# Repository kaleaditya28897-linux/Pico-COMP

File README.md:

# Pico-COMP

**A modern take on the TRS-80 Model 100: a text-only, battery-powered portable computer built on two
Raspberry Pi RP2350 microcontrollers.**

Pico-COMP is a clamshell laptop for writing and focused work: a full-size mechanical keyboard, a 7"
display driven in 80-column text mode (amber, green or white on black), a week of standby on a 2S2P
18650 pack, and Wi-Fi for mail, chat and file sync. Everything is programmed in C on the RP2350's RISC-V
cores, and every board, case part and keycap is generated from scripts in this repository.

> **Status (Nov 2026):** both boards, the switch plate, keycaps and battery spec are ready to order. The
> main board is routed and passes ERC, DRC (with schematic parity) and a power-copper audit; the case
> prints wait for the measured battery pack and display. Firmware: display driver and project skeleton.

| Part | State |
|---|---|
| Keyboard PCB (2 layers) | Routed, KiCad DRC 0 / ERC 0, fab package in `hardware/fab/keyboard/` |
| Switch plate | Laser-cut DXF ready (1.2 mm) |
| Keycaps (75) | Print-ready STEP/STL with debossed legends + inlays |
| Main board (6 layers) | Routed, ERC 0 / DRC 0 / power audit pass, fab package + order sheet in `hardware/fab/mainboard/` |
| Case | Parametric FreeCAD assembly, printable parts, no interferences |
| Firmware | Builds for both MCUs; HSTX DVI text driver (untested on hardware) |

---

## Features

- **Display:** 7" 1024x600 IPS HDMI panel fed 720x400 / 640x480 DVI straight from the RP2350's HSTX
  peripheral, as 80x25 / 80x30 text; amber-on-black, green-on-black and black-on-white schemes.
- **Keyboard:** 75 keys, Kailh Choc V1 low-profile switches at 17 mm pitch, inverted-T arrows (the only
  navigation), Fn layer for hotkeys, Kailh plate-mount stabilizers on Shift and Space.
- **Storage:** 64 GB soldered eMMC (internal disk) plus a microSD slot for extra space / file exchange;
  16 MB QSPI flash per MCU for firmware.
- **Wireless:** Wi-Fi 4 + Bluetooth 5.2 (Raspberry Pi RM2 / CYW43439, the Pico 2 W radio).
- **USB:**
  - USB-C port 1: dual-role (TUSB320). Device mode for charging, flashing, file transfer and serial;
    host mode for USB printers, barcode scanners and keyboards.
  - USB-C port 2: the network MCU's own USB.
- **Power:** custom 2S2P 18650 pack (7.4 V, 44 Wh), TI BQ25798 USB-C buck-boost charger, 5 V and 3.3 V
  buck converters, switched panel power for standby. Target: one week standby, ~4 days of normal use.
- **Buttons:** a real power button (charger ship mode disconnects the pack through a ship FET; press to
  turn on, hold 10 s for a hardware power cycle) and a system-reset pinhole that resets both MCUs.
- **I/O:** serial printer port (JST-SH, UART with RTS/CTS), expansion header (6 GPIO + I2C/SPI),
  piezo beeper.
- **Software (planned):** text editor, spreadsheet, database, mail, IM (IRC/Matrix), file sync web
  page, scheduler, todo, BASIC calculator, SSH/terminal, Gopher/Gemini, RSS, games. See `intent.md`.

## Architecture

Two RP2350s split the work so the UI never stalls on the network:

```
            USB-C 1 (dual-role)            HDMI (internal) -> 7" panel
                  |                              ^
   +--------------+------------------------------+--------------------+
   |  UI MCU: RP2350B (QFN-80)                                        |
   |  HSTX DVI text display, all apps, eMMC 64 GB (PIO 4-bit),        |
   |  microSD (SPI0), printer UART1, expansion, beeper, panel power   |
   +--------------+---------------------------------+-----------------+
                  | UART0 link (framed packets)     | SWD (UI reflashes NET)
   +--------------+---------------------------------+-----------------+
   |  NET MCU: RP2350A (QFN-60)                                       |
   |  Wi-Fi/BT (RM2, PIO gSPI), keyboard matrix scan (6x14),          |
   |  BQ25798 charger + TUSB320 over I2C, USB-C 2                     |
   +-------------------------------------------------------------------+
```

- Inter-MCU protocol: `[0xA5][type][len][payload][crc8]`, see `firmware/common/link.h`.
- Full GPIO map for both MCUs: `firmware/common/pins.h`.
- Design notes: `docs/architecture.md`, `docs/hardware-plan.md`.

## Firmware updates

- **Normal update:** connect USB-C port 1 to a computer. An "update firmware" hotkey (or
  `picotool reboot -u`) puts the UI MCU into the RP2350 USB bootloader, where it appears as a drive. Copy
  one `.uf2`. The UI image carries the NET MCU firmware and rewrites it over SWD when the version differs.
- **Recovery:** double-tap the system-reset button through the pinhole in the right side wall, which
  brings up the USB update drive (`pico_bootsel_via_double_reset`). If anything hangs, hold the power
  button for 10 s: the charger power-cycles the whole machine. BOOTSEL buttons inside the case are the last
  resort.
- **NET MCU direct:** USB-C port 2.

## Repository layout

```
firmware/            C firmware (Pico SDK, RISC-V)
  ui/                UI MCU: HSTX DVI text driver, font, main
  net/               NET MCU (stub)
  common/            link protocol, pin map
  boards/            pico_comp.h board header (16 MB flash, per-target RP2350A/B)
hardware/
  keyboard/          layout.py (single source of key positions), PCB + schematic generators
  mainboard/         PCB + schematic generators, fan-out, routers (Freerouting driver, maze router)
  kicad/             KiCad 10 projects, project libraries (footprints, symbols, 3D models), helpers
  mechanical/        FreeCAD case/assembly generator, keycaps, renders, print files
  fab/               fabrication packages and order sheets
  placement.py       where the boards sit in the case
docs/                architecture, hardware plan, routing guide, case dimensions
tools/               font converter
```

## Building the firmware

Requirements: [Raspberry Pi Pico SDK](https://github.com/raspberrypi/pico-sdk) 2.x and a RISC-V
toolchain (`riscv32-unknown-elf`, as distributed for the Pico SDK).

```sh
export PICO_SDK_PATH=~/pico-sdk          # default
export RISCV_TC=~/toolchains/riscv        # default
./build.sh
# -> build/firmware/ui/comp_ui.uf2, build/firmware/net/comp_net.uf2
cmake --build build --target comp_ui     # rebuild one target
```

Firmware is C11 only. The board header `firmware/boards/pico_comp.h` describes this hardware; the UI
target is built for the RP2350B package (`PICO_RP2350A=0`).

## Hardware

Nothing under `hardware/` is drawn by hand: every board, schematic, footprint, 3D model, case part and
keycap is generated by the Python scripts next to it, and opened and checked in KiCad / FreeCAD.

| Board | Size | Layers | Notes |
|---|---|---|---|
| Main board | 152 x 84 mm | 6 (sig / GND / sig / sig / 3V3 / sig) | 5-mil rules, 0.45/0.2 vias, via-in-pad under the eMMC BGA |
| Keyboard | 244 x 120 mm | 2 | 75 Choc V1 (top, THT), 75 diodes (bottom, SMD) |

Key parts: RP2350A + RP2350B, W25Q128JV flash x2, BQ25798 charger, TPS62933 (5 V) and AP63203 (3.3 V)
bucks, TPS22917 panel switch, TUSB320 USB-C controller, Raspberry Pi RM2, 64 GB eMMC (Kimtigo
KM110SS1064GxA), Hirose microSD, Molex HDMI, HRO USB-C x2, XT30 battery connector.

### Tools
- KiCad 10 (with `pcbnew` Python), FreeCAD 1.x (`FreeCADCmd`), Java 21 + Freerouting 2.1 (routing only).

### Regenerating
The full order is at the end of `docs/hardware-plan.md`. In short:

```sh
python3 hardware/keyboard/layout.py                        # key positions, plate.dxf
python3 hardware/kicad/make_footprints.py                  # RM2, Choc and stabilizer footprints
FreeCADCmd hardware/kicad/make_3d.py                       # STEP models missing from KiCad's library
python3 hardware/mainboard/gen_pcb.py && python3 hardware/mainboard/gen_sch.py
python3 hardware/keyboard/gen_pcb.py  && python3 hardware/keyboard/gen_sch.py
python3 hardware/mainboard/fanout.py hardware/kicad/mainboard.kicad_pcb    # plane, BGA, dog-bone fan-out
ROUTE_EXTRA=--router.job_timeout=00:40:00 python3 hardware/mainboard/route.py hardware/kicad/<board>.kicad_pcb 40
python3 hardware/mainboard/maze_route.py hardware/kicad/<board>.kicad_pcb  # finish leftovers (route_from.py)
python3 hardware/mainboard/route.py --prune hardware/kicad/<board>.kicad_pcb
python3 hardware/mainboard/check_power.py hardware/kicad/mainboard.kicad_pcb  # power-copper gate
sh hardware/kicad/fab.sh                                   # ERC/DRC gate + all fab outputs
python3 hardware/kicad/export_parts.py && FreeCADCmd hardware/mechanical/case.py
FreeCAD hardware/mechanical/open_gui.py                    # open the assembly (saves colours)
```

Schematic and PCB are generated from one netlist and linked symbol-to-footprint, so ERC and
schematic-parity DRC must stay at zero. `fab.sh` refuses to export a board that fails either.

### Case and keycaps
- Laptop-style split: bottom tub (D-cover), top deck (C-cover) flush with the rim, lid shell + back
  cover, hinge on a steel pin. 250 x 140 mm footprint, 52 mm closed.
- Printable parts (STEP + STL) in `hardware/mechanical/print/`: base, deck, lid, lid back.
- Keycaps in `hardware/mechanical/keycaps/`: Choc V1 stems, legends debossed 0.5 mm with matching
  inlay bodies for two-colour printing; Shift/Space carry stabilizer pegs.
- Review renders: `FreeCADCmd hardware/mechanical/render_export.py && python3 hardware/mechanical/render.py`.

## Ordering

Everything is set up for [robu.in](https://robu.in) (PCB fab + assembly, laser cutting, 3D printing,
custom Li-ion packs); the files are standard and work with any fab.

- What goes where: `hardware/fab/ORDER-CHECKLIST.md`
- Keyboard PCB order sheet: `hardware/fab/keyboard/ORDER.md` (assemble the diodes only; the switches
  are soldered after they are clipped into the plate)

## Open items

- Measure the display module (thickness, outline) and the HDMI cable; adjust the lid.
- Size the battery bay to the delivered pack.
- Firmware: key scanner, UART link, eMMC (PIO SD/MMC) and USB host drivers, NET reflash over SWD,
  file system, apps; power key (GPIO37) and power-off via the charger's ship mode (SDRV_CTRL = 10),
  charge-current limit (<= 2 A, the BAT copper is sized for it).

## Credits

Designed by Aditya Kale. Terminus font (SIL OFL 1.1). Built on the Raspberry Pi Pico SDK, KiCad,
FreeCAD and Freerouting.

© 2026 Aditya Kale. Licensed under the GNU General Public License v3.0, see [LICENSE](LICENSE).

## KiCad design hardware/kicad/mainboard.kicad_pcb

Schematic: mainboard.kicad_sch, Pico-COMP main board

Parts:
BZ1: Piezo; Buzzer_Murata_PKMCS0909E; MPN PKMCS0909E4000-R1
C11, C12, C13, C14, C15, C16, C17, C18, C19, C21, C22, C23, C24, C25, C26, C27, C28, C29, C62, C71, C80, C90, C100, C110, C111, C113, C114, C122, C222: 100nF; C_0402_1005Metric
C50, C51, C52, C53, C57, C58, C59, C60, C61, C68, C70, C81, C510: 10uF; C_0805_2012Metric
C54, C55: 47nF; C_0402_1005Metric
C56, C112, C115: 4.7uF; C_0603_1608Metric
C63, C512: 10nF; C_0402_1005Metric
C64, C65, C66, C72, C73, C74: 22uF; C_0805_2012Metric
C67, C116: 1uF; C_0402_1005Metric
C69: 1nF; C_0402_1005Metric
C120, C121, C220, C221: 4.7uF; C_0402_1005Metric_RPi_Wide; MPN GRM155R60J475ME47D
C123, C124, C223, C224: 15pF; C_0402_1005Metric
C125, C225: 4.7uF; C_0402_1005Metric; MPN GRM155R60J475ME47D
D1: PWR; LED_0603_1608Metric
D2: UI; LED_0603_1608Metric
D50, D51: BAT54C; SOT-23; MPN BAT54C
F1, F2: W25Q128JVS; SOIC-8_5.3x5.3mm_P1.27mm; MPN W25Q128JVSIQ
FID1, FID2, FID3: Fiducial; Fiducial_1mm_Mask2mm
H1, H2, H3, H4: M2.5; MountingHole_2.7mm_M2.5
J1: USB-C; USB_C_Receptacle_HRO_TYPE-C-31-M-12; MPN TYPE-C-31-M-12
J2: BATTERY 2S; AMASS_XT30PW-M_1x02_P2.50mm_Horizontal; MPN XT30PW-M
J3, J4: SWD; PinHeader_1x03_P1.27mm_Vertical_SMD_Pin1Left
J5: NTC; JST_PH_B2B-PH-K_1x02_P2.00mm_Vertical; MPN B2B-PH-K-S
J6: HDMI to panel; HDMI_A_Molex_208658-1001_Horizontal; MPN 2086581001
J7: PANEL 5V; JST_PH_B2B-PH-K_1x02_P2.00mm_Vertical; MPN B2B-PH-K-S
J8: AUX 5V; JST_PH_B2B-PH-K_1x02_P2.00mm_Vertical; MPN B2B-PH-K-S
J9: microSD; microSD_HC_Hirose_DM3AT-SF-PEJM5; MPN DM3AT-SF-PEJM5
J11: KB_MATRIX; PinHeader_1x20_P2.54mm_Horizontal
J12: PRINTER; JST_SH_SM06B-SRSS-TB_1x06-1MP_P1.00mm_Horizontal; MPN SM06B-SRSS-TB
J13: EXPANSION; PinHeader_1x10_P1.27mm_Vertical
J14: USB-C NET; USB_C_Receptacle_HRO_TYPE-C-31-M-12; MPN TYPE-C-31-M-12
L1, L2: 3.3uH; L_Abracon_AOTA-B201610S_RPi; MPN AOTA-B201610S3R3-101-T
L5: 2.2uH; L_Bourns_SRP7028A_7.3x6.6mm; MPN SRP7028A-2R2M
L6: 4.7uH; L_Bourns_SRP7028A_7.3x6.6mm; MPN SRP7028A-4R7M
L7: 4.7uH; L_Bourns_SRN6045TA; MPN SRN6045TA-4R7M
Q50: CSD17581Q3A; VSON-8_3.3x3.3mm_P0.65mm_TI_Q3A; MPN CSD17581Q3A
R11, R12, R21, R22, R95: 1k; R_0402_1005Metric
R13, R23, R56, R57, R61, R90, R91, R92, R97, R110, R111, R112, R113, R114, R115, R130: 10k; R_0402_1005Metric
R14, R24: 33; R_0402_1005Metric
R50: 5.23k; R_0402_1005Metric
R51: 30.1k; R_0402_1005Metric
R52, R53, R116, R117, R118, R119: 47k; R_0402_1005Metric
R54, R55, R70: 4.7k; R_0402_1005Metric
R58: 8.2k; R_0402_1005Metric
R59, R98: 100; R_0402_1005Metric
R60: 52.3k; R_0402_1005Metric
R80, R81, R82, R83, R84, R85, R86, R87: 270; R_0402_1005Metric
R96: 470; R_0402_1005Metric
R99: 100k; R_0402_1005Metric
R100: 887k; R_0402_1005Metric
RCC3, RCC4: 5.1k; R_0402_1005Metric
RNU1, RNU2: 27; R_0402_1005Metric
RUD1, RUD2: 27; R_0402_1005Metric
SW1, SW3: BOOTSEL; SW_SPST_B3U-1000P; MPN B3U-1000P
SW2: RESET; Panasonic_EVQPUJ_EVQPUA; MPN EVQ-PUJ02K
SW4: RESET; SW_SPST_B3U-1000P; MPN B3U-1000P
SW5: POWER; Panasonic_EVQPUJ_EVQPUA; MPN EVQ-PUJ02K
U1: RP2350B (UI); QFN-80-1EP_10x10mm_P0.4mm_EP3.4x3.4mm; MPN RP2350B
U2: RP2350A (NET); QFN-60-1EP_7x7mm_P0.4mm_EP3.4x3.4mm; MPN RP2350A
U3, U11: USBLC6-2SC6; SOT-23-6; MPN USBLC6-2SC6
U5: BQ25798; Texas_RQM0029A_VQFN-29_4x4mm_P0.4mm; MPN BQ25798RQMR
U6: TPS62933; SOT-583-8; MPN TPS62933DRLR
U7: AP63203WU; TSOT-23-6; MPN AP63203WU-7
U8: RM2; RaspberryPi_RM2; MPN RMC20452T
U9: TPS22917; SOT-23-6; MPN TPS22917DBVR
U10: TUSB320; Texas_X2QFN-12_1.6x1.6mm_P0.4mm; MPN TUSB320LAIRWBR
U12: eMMC 64GB; LFBGA-153_11.5x13mm_Layout14x14_P0.5mm; MPN KM110SS1064GxA-DDD00WT
Y1, Y2: 12MHz; Crystal_SMD_3225-4Pin_3.2x2.5mm; MPN ABM8-272-T3

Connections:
BST3: C71.1, U7.6 (BST)
BST5: C62.1, U6.6 (BST)
BTST1: C54.1, U5.4 (BTST1)
BTST2: C55.1, U5.19 (BTST2)
BUZZ: R98.1, U1.27 (GPIO26)
BUZZ_R: BZ1.1 (+), R98.2
CC1: J1.A5 (CC1), U10.1 (CC1)
CC2: J1.B5 (CC2), U10.2 (CC2)
CC3: J14.A5 (CC1), RCC3.1
CC4: J14.B5 (CC2), RCC4.1
CHG_INT: R56.2, U2.34 (GPIO22), U5.21 (~INT), U10.6 (~INT/OUT3)
CHG_STAT: R57.2, U2.41 (GPIO27/ADC1), U5.1 (STAT)
COL0: J11.7, U2.9 (GPIO6)
COL1: J11.8, U2.10 (GPIO7)
COL2: J11.9, U2.12 (GPIO8)
COL3: J11.10, U2.13 (GPIO9)
COL4: J11.11, U2.14 (GPIO10)
COL5: J11.12, U2.15 (GPIO11)
COL6: J11.13, U2.16 (GPIO12)
COL7: J11.14, U2.17 (GPIO13)
COL8: J11.15, U2.18 (GPIO14)
COL9: J11.16, U2.19 (GPIO15)
COL10: J11.17, U2.27 (GPIO16)
COL11: J11.18, U2.28 (GPIO17)
COL12: J11.19, U2.29 (GPIO18)
COL13: J11.20, U2.31 (GPIO19)
EMMC_CLK: U1.38 (GPIO30), U12.M6 (CLK)
EMMC_CMD: R110.2, U1.39 (GPIO31), U12.M5 (CMD)
EMMC_DAT0: R111.2, U1.40 (GPIO32), U12.A3 (DAT0)
EMMC_DAT1: R112.2, U1.42 (GPIO33), U12.A4 (DAT1)
EMMC_DAT2: R113.2, U1.43 (GPIO34), U12.A5 (DAT2)
EMMC_DAT3: R114.2, U1.44 (GPIO35), U12.B2 (DAT3)
EMMC_DAT4: R116.2, U12.B3 (DAT4)
EMMC_DAT5: R117.2, U12.B4 (DAT5)
EMMC_DAT6: R118.2, U12.B5 (DAT6)
EMMC_DAT7: R119.2, U12.B6 (DAT7)
EMMC_RST: R115.2, U1.45 (GPIO36), U12.K5 (RSTN)
EMMC_VDDI: C116.1, U12.C2 (VDDi)
EXP0: J13.3, U1.77 (GPIO0)
EXP1: J13.4, U1.78 (GPIO1)
EXP2: J13.5, U1.79 (GPIO2)
EXP3: J13.6, U1.80 (GPIO3)
EXP8: J13.7, U1.6 (GPIO8)
EXP9: J13.8, U1.7 (GPIO9)
FB5: R60.2, R61.1, U6.8 (FB)
GND: BZ1.2 (-), C11.2, C12.2, C13.2, C14.2, C15.2, C16.2, C17.2, C18.2, C19.2, C21.2, C22.2, C23.2, C24.2, C25.2, C26.2, C27.2, C28.2, C29.2, C50.2, C51.2, C52.2, C53.2, C56.2, C57.2, C58.2, C59.2, C60.2, C61.2, C63.2, C64.2, C65.2, C66.2, C67.2, C68.2, C69.2, C70.2, C72.2, C73.2, C74.2, C80.2, C81.2, C90.2, C100.2, C110.2, C111.2, C112.2, C113.2, C114.2, C115.2, C116.2, C120.2, C121.2, C122.2, C123.2, C124.2, C125.2, C220.2, C221.2, C222.2, C223.2, C224.2, C225.2, C510.2, C512.2, D1.1 (K), D2.1 (K), F1.4 (GND), F2.4 (GND), J1.A1 (GND), J1.A12 (GND), J1.B1 (GND), J1.B12 (GND), J1.SH (SHIELD), J2.2, J3.2, J4.2, J5.2, J6.2 (D2S), J6.5 (D1S), J6.8 (D0S), J6.11 (CKS), J6.17 (GND), J6.SH, J7.2, J8.2, J9.6 (VSS), J9.10 (DET_A), J9.SH (SHIELD), J12.6, J12.MP (MountPin), J13.2, J13.9, J14.A1 (GND), J14.A12 (GND), J14.B1 (GND), J14.B12 (GND), J14.SH (SHIELD), R51.2, R53.2, R58.2, R61.2, R99.2, RCC3.2, RCC4.2, SW1.2, SW2.2, SW3.2, SW4.2, SW5.2, U1.62 (VREG_PGND), U1.81 (GND), U2.47 (VREG_PGND), U2.61 (GND), U3.2 (GND), U5.10 (ACDRV2), U5.11 (ACDRV1), U5.13 (~CE), U5.27 (GND), U6.4 (GND), U7.4 (GND), U8.1 (GND), U8.4 (GND), U8.7 (GND), U8.11 (GND), U8.15 (GND), U8.21 (GND), U9.2 (GND), U10.5 (ADDR), U10.10 (GND), U10.11 (~EN), U11.2 (GND), U12.A6 (GND), U12.C4 (GND), U12.E7 (GND), U12.G5 (GND), U12.H10 (GND), U12.J5 (GND), U12.K8 (GND), U12.N2 (GND)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
HD_CKN: J6.12 (CK-), R83.2
HD_CKP: J6.10 (CK+), R82.2
HD_D0N: J6.9 (D0-), R81.2
HD_D0P: J6.7 (D0+), R80.2
HD_D1N: J6.6 (D1-), R87.2
HD_D1P: J6.4 (D1+), R86.2
HD_D2N: J6.3 (D2-), R85.2
HD_D2P: J6.1 (D2+), R84.2
I2C_SCL: R55.2, U2.33 (GPIO21), U5.14 (SCL), U10.8 (SCL/OUT2)
I2C_SDA: R54.2, U2.32 (GPIO20), U5.15 (SDA), U10.7 (SDA/OUT1)
ILIM: R52.2, R53.1, U5.17 (ILIM_HIZ)
NET_1V1: C28.1, C29.1, C220.1, L2.1, U2.6 (DVDD), U2.23 (DVDD), U2.39 (DVDD), U2.50 (VREG_FB)
NET_AVDD: C225.1, R24.2, U2.46 (VREG_AVDD)
NET_BOOT: R22.2, SW3.1
NET_LX: L2.2, U2.48 (VREG_LX)
NET_QSCK: F2.6 (CLK), U2.56 (QSPI_SCLK)
NET_QSD0: F2.5 (DI/IO_{0}), U2.57 (QSPI_SD0)
NET_QSD1: F2.2 (DO/IO_{1}), U2.59 (QSPI_SD1)
NET_QSD2: F2.3 (~WP/IO_{2}), U2.58 (QSPI_SD2)
NET_QSD3: F2.7 (~HOLD/~RESET/IO_{3}), U2.55 (QSPI_SD3)
NET_QSS: F2.1 (~CS), R22.1, U2.60 (~QSPI_SS)
NET_RUN: D51.2, R23.2, SW4.1, U2.26 (RUN)
NET_SWCLK: J4.1, U1.8 (GPIO10), U2.24 (SWCLK)
NET_SWDIO: J4.3, U1.9 (GPIO11), U2.25 (SWDIO)
NET_USB_MCU_N: RNU2.1, U2.51 (USB_DM)
NET_USB_MCU_P: RNU1.1, U2.52 (USB_DP)
NET_USB_N: J14.A7 (D-), J14.B7 (D-), RNU2.2, U11.3 (I/O2), U11.4 (I/O2)
NET_USB_P: J14.A6 (D+), J14.B6 (D+), RNU1.2, U11.1 (I/O1), U11.6 (I/O1)
NET_XB: C224.1, R21.1, Y2.3
NET_XIN: C223.1, U2.21 (XIN), Y2.1
NET_XOUT: R21.2, U2.22 (XOUT)
PANEL_CT: C69.1, U9.4 (CT)
PANEL_EN: R99.1, U1.28 (GPIO27), U9.3 (ON)
PMID: C52.1, C53.1, U5.29 (PMID)
PRN_CTS: J12.5, U1.3 (GPIO6)
PRN_RTS: J12.4, U1.4 (GPIO7)
PRN_RX: J12.3, U1.2 (GPIO5)
PRN_TX: J12.2, U1.1 (GPIO4)
PROG: R58.1, U5.20 (PROG)
PWR_KEY: D50.3, SW5.1
PWR_LED: D1.2 (A), R70.2
QON: C512.1, D50.1, U5.12 (~QON)
REGN: C56.1, R50.1, R52.1, U5.5 (REGN)
ROW0: J11.1, U2.2 (GPIO0)
ROW1: J11.2, U2.3 (GPIO1)
ROW2: J11.3, U2.4 (GPIO2)
ROW3: J11.4, U2.5 (GPIO3)
ROW4: J11.5, U2.7 (GPIO4)
ROW5: J11.6, U2.8 (GPIO5)
SDRV: Q50.4 (G), U5.24 (SDRV)
SD_CS: J9.2 (DAT3/CD), R92.2, U1.21 (GPIO21)
SD_DET: J9.9 (DET_B), U1.25 (GPIO24)
SD_MISO: J9.7 (DAT0), U1.20 (GPIO20)
SD_MOSI: J9.3 (CMD), U1.23 (GPIO23)
SD_NC1: J9.8 (DAT1), R90.2
SD_NC2: J9.1 (DAT2), R91.2
SD_SCK: J9.5 (CLK), U1.22 (GPIO22)
SS5: C63.1, U6.7 (SS)
SW1: C54.2, L5.1, U5.28 (SW1)
SW2: C55.2, L5.2, U5.26 (SW2)
SW3: C71.2, L7.1, U7.5 (SW)
SW5: C62.2, L6.1, U6.5 (SW)
SYS_RST: D51.3, SW2.1
TMDS_CKN: R83.1, U1.14 (GPIO15)
TMDS_CKP: R82.1, U1.13 (GPIO14)
TMDS_D0N: R81.1, U1.12 (GPIO13)
TMDS_D0P: R80.1, U1.11 (GPIO12)
TMDS_D1N: R87.1, U1.19 (GPIO19)
TMDS_D1P: R86.1, U1.18 (GPIO18)
TMDS_D2N: R85.1, U1.17 (GPIO17)
TMDS_D2P: R84.1, U1.16 (GPIO16)
TS: J5.1, R50.2, R51.1, U5.16 (TS)
UI_1V1: C18.1, C19.1, C120.1, L1.1, U1.10 (DVDD), U1.32 (DVDD), U1.51 (DVDD), U1.65 (VREG_FB)
UI_AVDD: C125.1, R14.2, U1.61 (VREG_AVDD)
UI_BOOT: R12.2, SW1.1
UI_LED: R95.1, U1.26 (GPIO25)
UI_LEDK: D2.2 (A), R95.2
UI_LX: L1.2, U1.63 (VREG_LX)
UI_PWR_KEY: D50.2, R130.2, U1.46 (GPIO37)
UI_QSCK: F1.6 (CLK), U1.71 (QSPI_SCLK)
UI_QSD0: F1.5 (DI/IO_{0}), U1.72 (QSPI_SD0)
UI_QSD1: F1.2 (DO/IO_{1}), U1.74 (QSPI_SD1)
UI_QSD2: F1.3 (~WP/IO_{2}), U1.73 (QSPI_SD2)
UI_QSD3: F1.7 (~HOLD/~RESET/IO_{3}), U1.70 (QSPI_SD3)
UI_QSS: F1.1 (~CS), R12.1, U1.75 (~QSPI_SS)
UI_RUN: D51.1, R13.2, U1.35 (RUN)
UI_RX: U1.37 (GPIO29), U2.42 (GPIO28/ADC2)
UI_SWCLK: J3.1, U1.33 (SWCLK)
UI_SWDIO: J3.3, U1.34 (SWDIO)
UI_TX: U1.36 (GPIO28), U2.43 (GPIO29/ADC3)
UI_USB_N: RUD2.2, U1.66 (USB_DM)
UI_USB_P: RUD1.2, U1.67 (USB_DP)
UI_XB: C124.1, R11.1, Y1.3
UI_XIN: C123.1, U1.30 (XIN), Y1.1
UI_XOUT: R11.2, U1.31 (XOUT)
USB_N: J1.A7 (D-), J1.B7 (D-), RUD2.1, U3.3 (I/O2), U3.4 (I/O2), U5.7 (D-)
USB_P: J1.A6 (D+), J1.B6 (D+), RUD1.1, U3.1 (I/O1), U3.6 (I/O1), U5.6 (D+)
V3V3: C11.1, C12.1, C13.1, C14.1, C15.1, C16.1, C17.1, C21.1, C22.1, C23.1, C24.1, C25.1, C26.1, C27.1, C72.1, C73.1, C74.1, C80.1, C81.1, C90.1, C100.1, C110.1, C111.1, C112.1, C113.1, C114.1, C115.1, C121.1, C122.1, C221.1, C222.1, F1.8 (VCC), F2.8 (VCC), J9.4 (VDD), J13.1, J13.10, L7.2, R13.1, R14.1, R23.1, R24.1, R54.1, R55.1, R56.1, R57.1, R70.1, R90.1, R91.1, R92.1, R110.1, R111.1, R112.1, R113.1, R114.1, R115.1, R116.1, R117.1, R118.1, R119.1, R130.1, U1.5 (IOVDD), U1.15 (IOVDD), U1.24 (IOVDD), U1.29 (IOVDD), U1.41 (IOVDD), U1.50 (IOVDD), U1.59 (ADC_AVDD), U1.60 (IOVDD), U1.64 (VREG_VIN), U1.68 (USB_OTP_VDD), U1.69 (QSPI_IOVDD), U1.76 (IOVDD), U2.1 (IOVDD), U2.11 (IOVDD), U2.20 (IOVDD), U2.30 (IOVDD), U2.38 (IOVDD), U2.44 (ADC_AVDD), U2.45 (IOVDD), U2.49 (VREG_VIN), U2.53 (USB_OTP_VDD), U2.54 (QSPI_IOVDD), U7.1 (FB), U8.14 (VDDIO), U8.16 (VIN), U10.12 (VDD), U12.C6 (VCCQ), U12.E6 (VCC), U12.F5 (VCC), U12.J10 (VCC), U12.K9 (VCC), U12.M4 (VCCQ), U12.N4 (VCCQ), U12.P3 (VCCQ), U12.P5 (VCCQ)
V5: C64.1, C65.1, C66.1, C67.1, C70.1, J8.1, J12.1, L6.2, R60.1, U7.2 (EN), U7.3 (IN), U9.1 (VIN)
V5_PANEL: C68.1, J6.18 (+5V), J7.1, U9.6 (VOUT)
VBAT: C59.1, C510.1, Q50.1 (S), Q50.2 (S), Q50.3 (S), U5.22 (BAT), U5.23 (BAT)
VBATP: R59.1, U5.18 (BATP)
VBAT_PACK: J2.1, Q50.5 (D), R59.2
VBUS: C50.1, C51.1, J1.A4 (VBUS), J1.A9 (VBUS), J1.B4 (VBUS), J1.B9 (VBUS), R100.1, U3.5 (VBUS), U5.2 (VBUS), U5.3 (VBUS), U5.8 (VAC2), U5.9 (VAC1)
VBUS2: J14.A4 (VBUS), J14.A9 (VBUS), J14.B4 (VBUS), J14.B9 (VBUS), U11.5 (VBUS)
VBUS_DET: R100.2, U10.4 (VBUS_DET)
VSYS: C57.1, C58.1, C60.1, C61.1, U5.25 (SYS), U6.2 (EN), U6.3 (VIN)
WL_CLK: U2.40 (GPIO26/ADC0), U8.3 (SCLK)
WL_CS: U2.37 (GPIO25), U8.9 (~CS)
WL_DATA: R96.1, R97.1, U2.36 (GPIO24), U8.5 (DATA_IN)
WL_DOUT: R96.2, U8.6 (DATA_OUT)
WL_IRQ: R97.2, U8.10 (~IRQ)
WL_ON: U2.35 (GPIO23), U8.12 (WL_ON), U8.13 (BT_ON)

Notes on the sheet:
USB-C input, protection, BQ25798 2S charger, ship FET, power button, battery
Rails: TPS62933 VSYS->5 V, AP63203 5 V->3.3 V, panel power
UI MCU (U1): display (HSTX->HDMI), microSD, printer, expansion, USB
NET MCU (U2): keyboard matrix, RM2 Wi-Fi, charger I2C
Mechanical
Power flags (ERC)

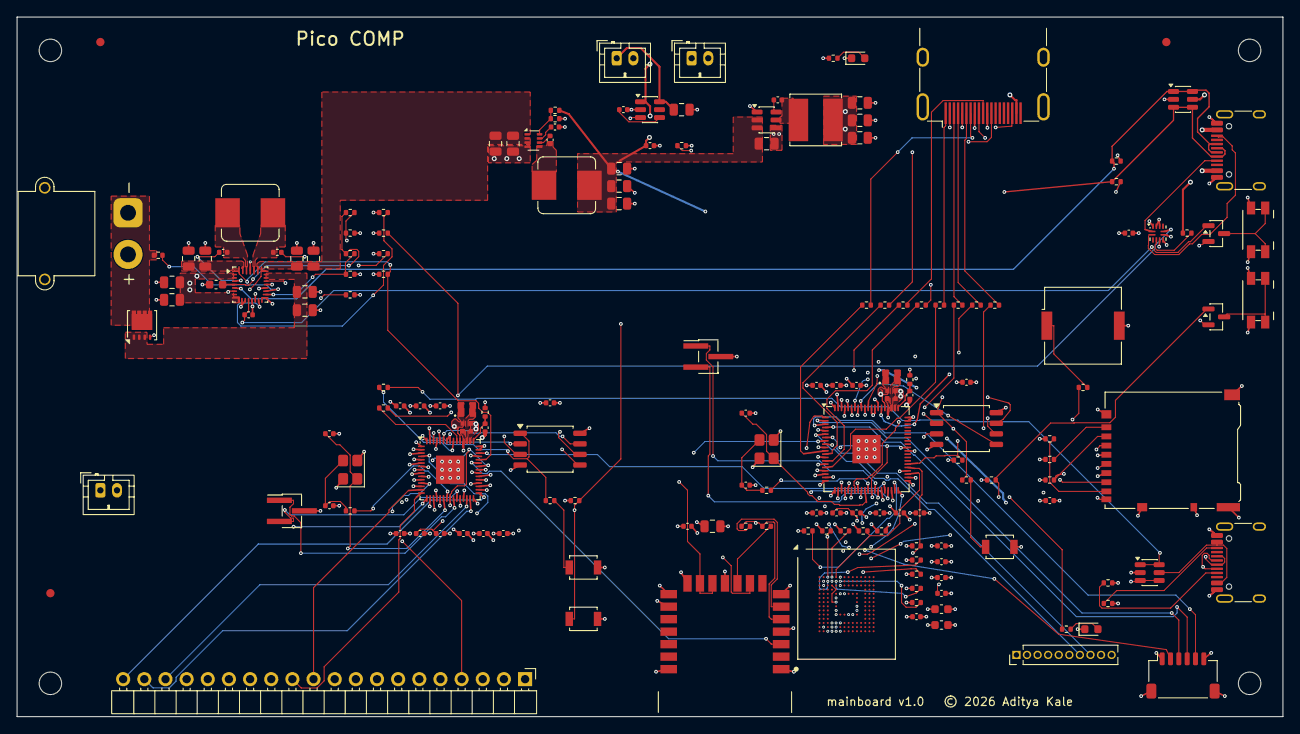
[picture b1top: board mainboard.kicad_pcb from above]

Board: 6 copper layers, 152.0 x 84.0 mm, 174 parts (0 on the bottom side), 159 nets.

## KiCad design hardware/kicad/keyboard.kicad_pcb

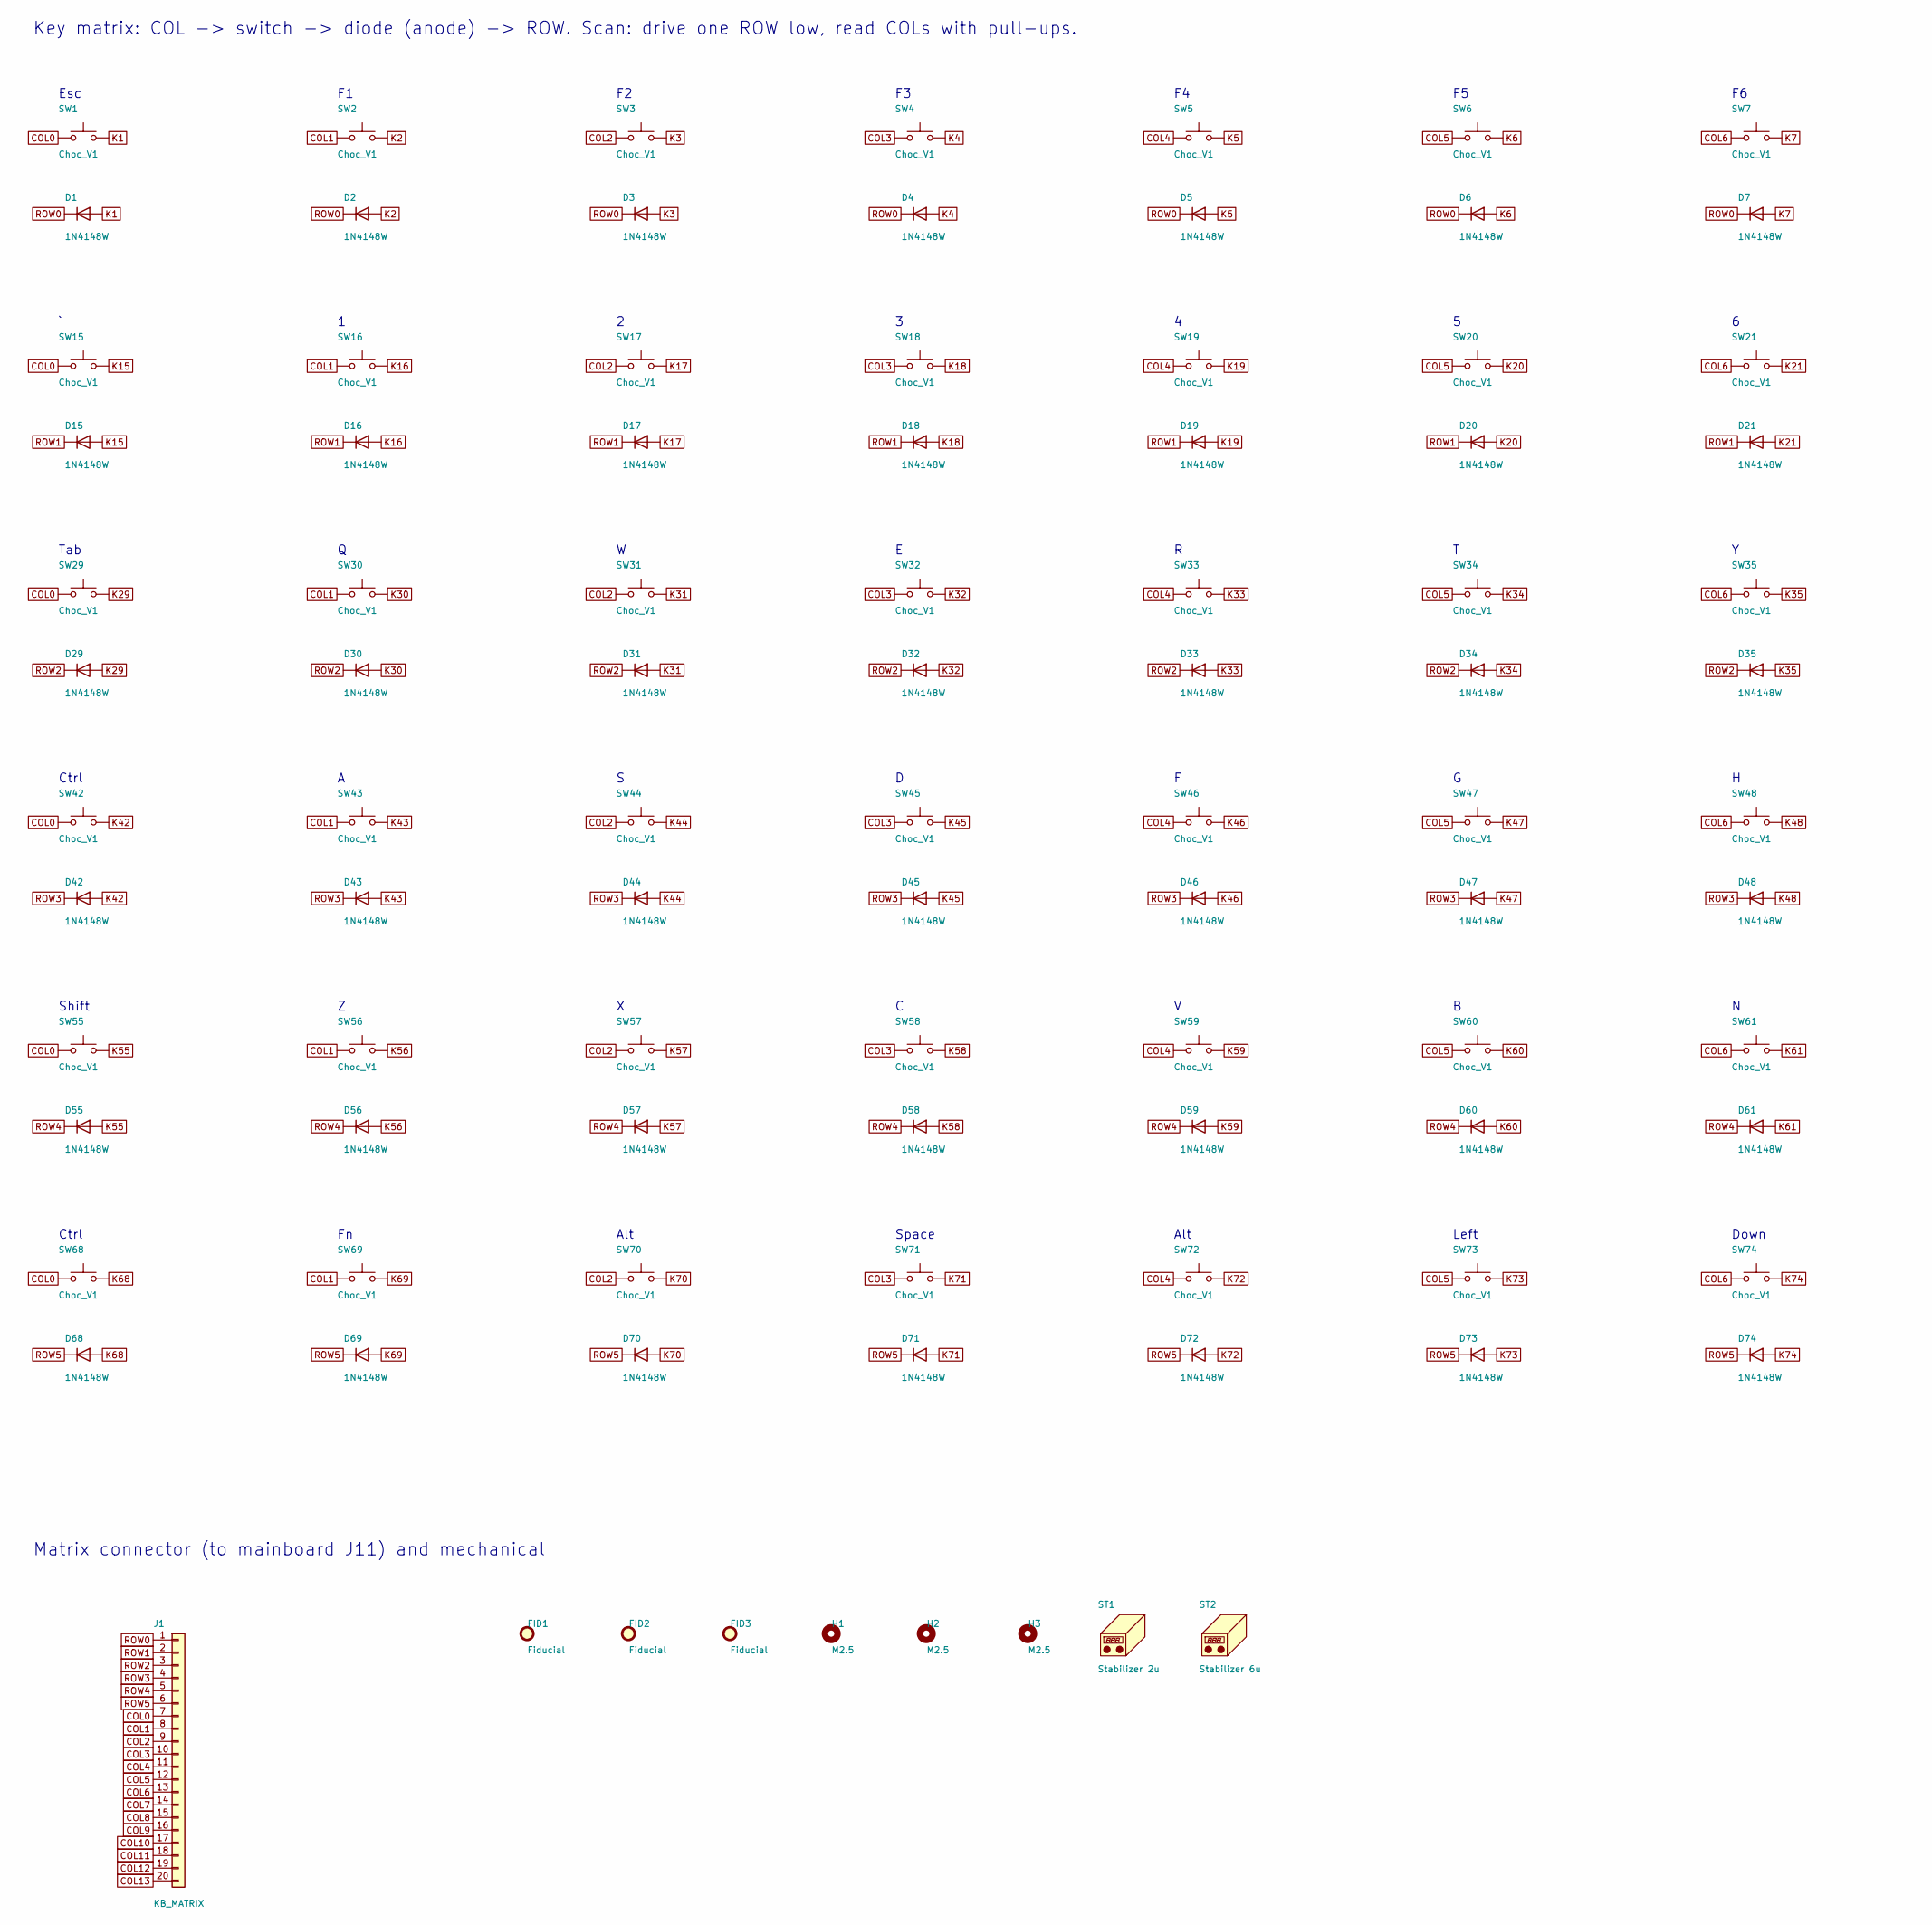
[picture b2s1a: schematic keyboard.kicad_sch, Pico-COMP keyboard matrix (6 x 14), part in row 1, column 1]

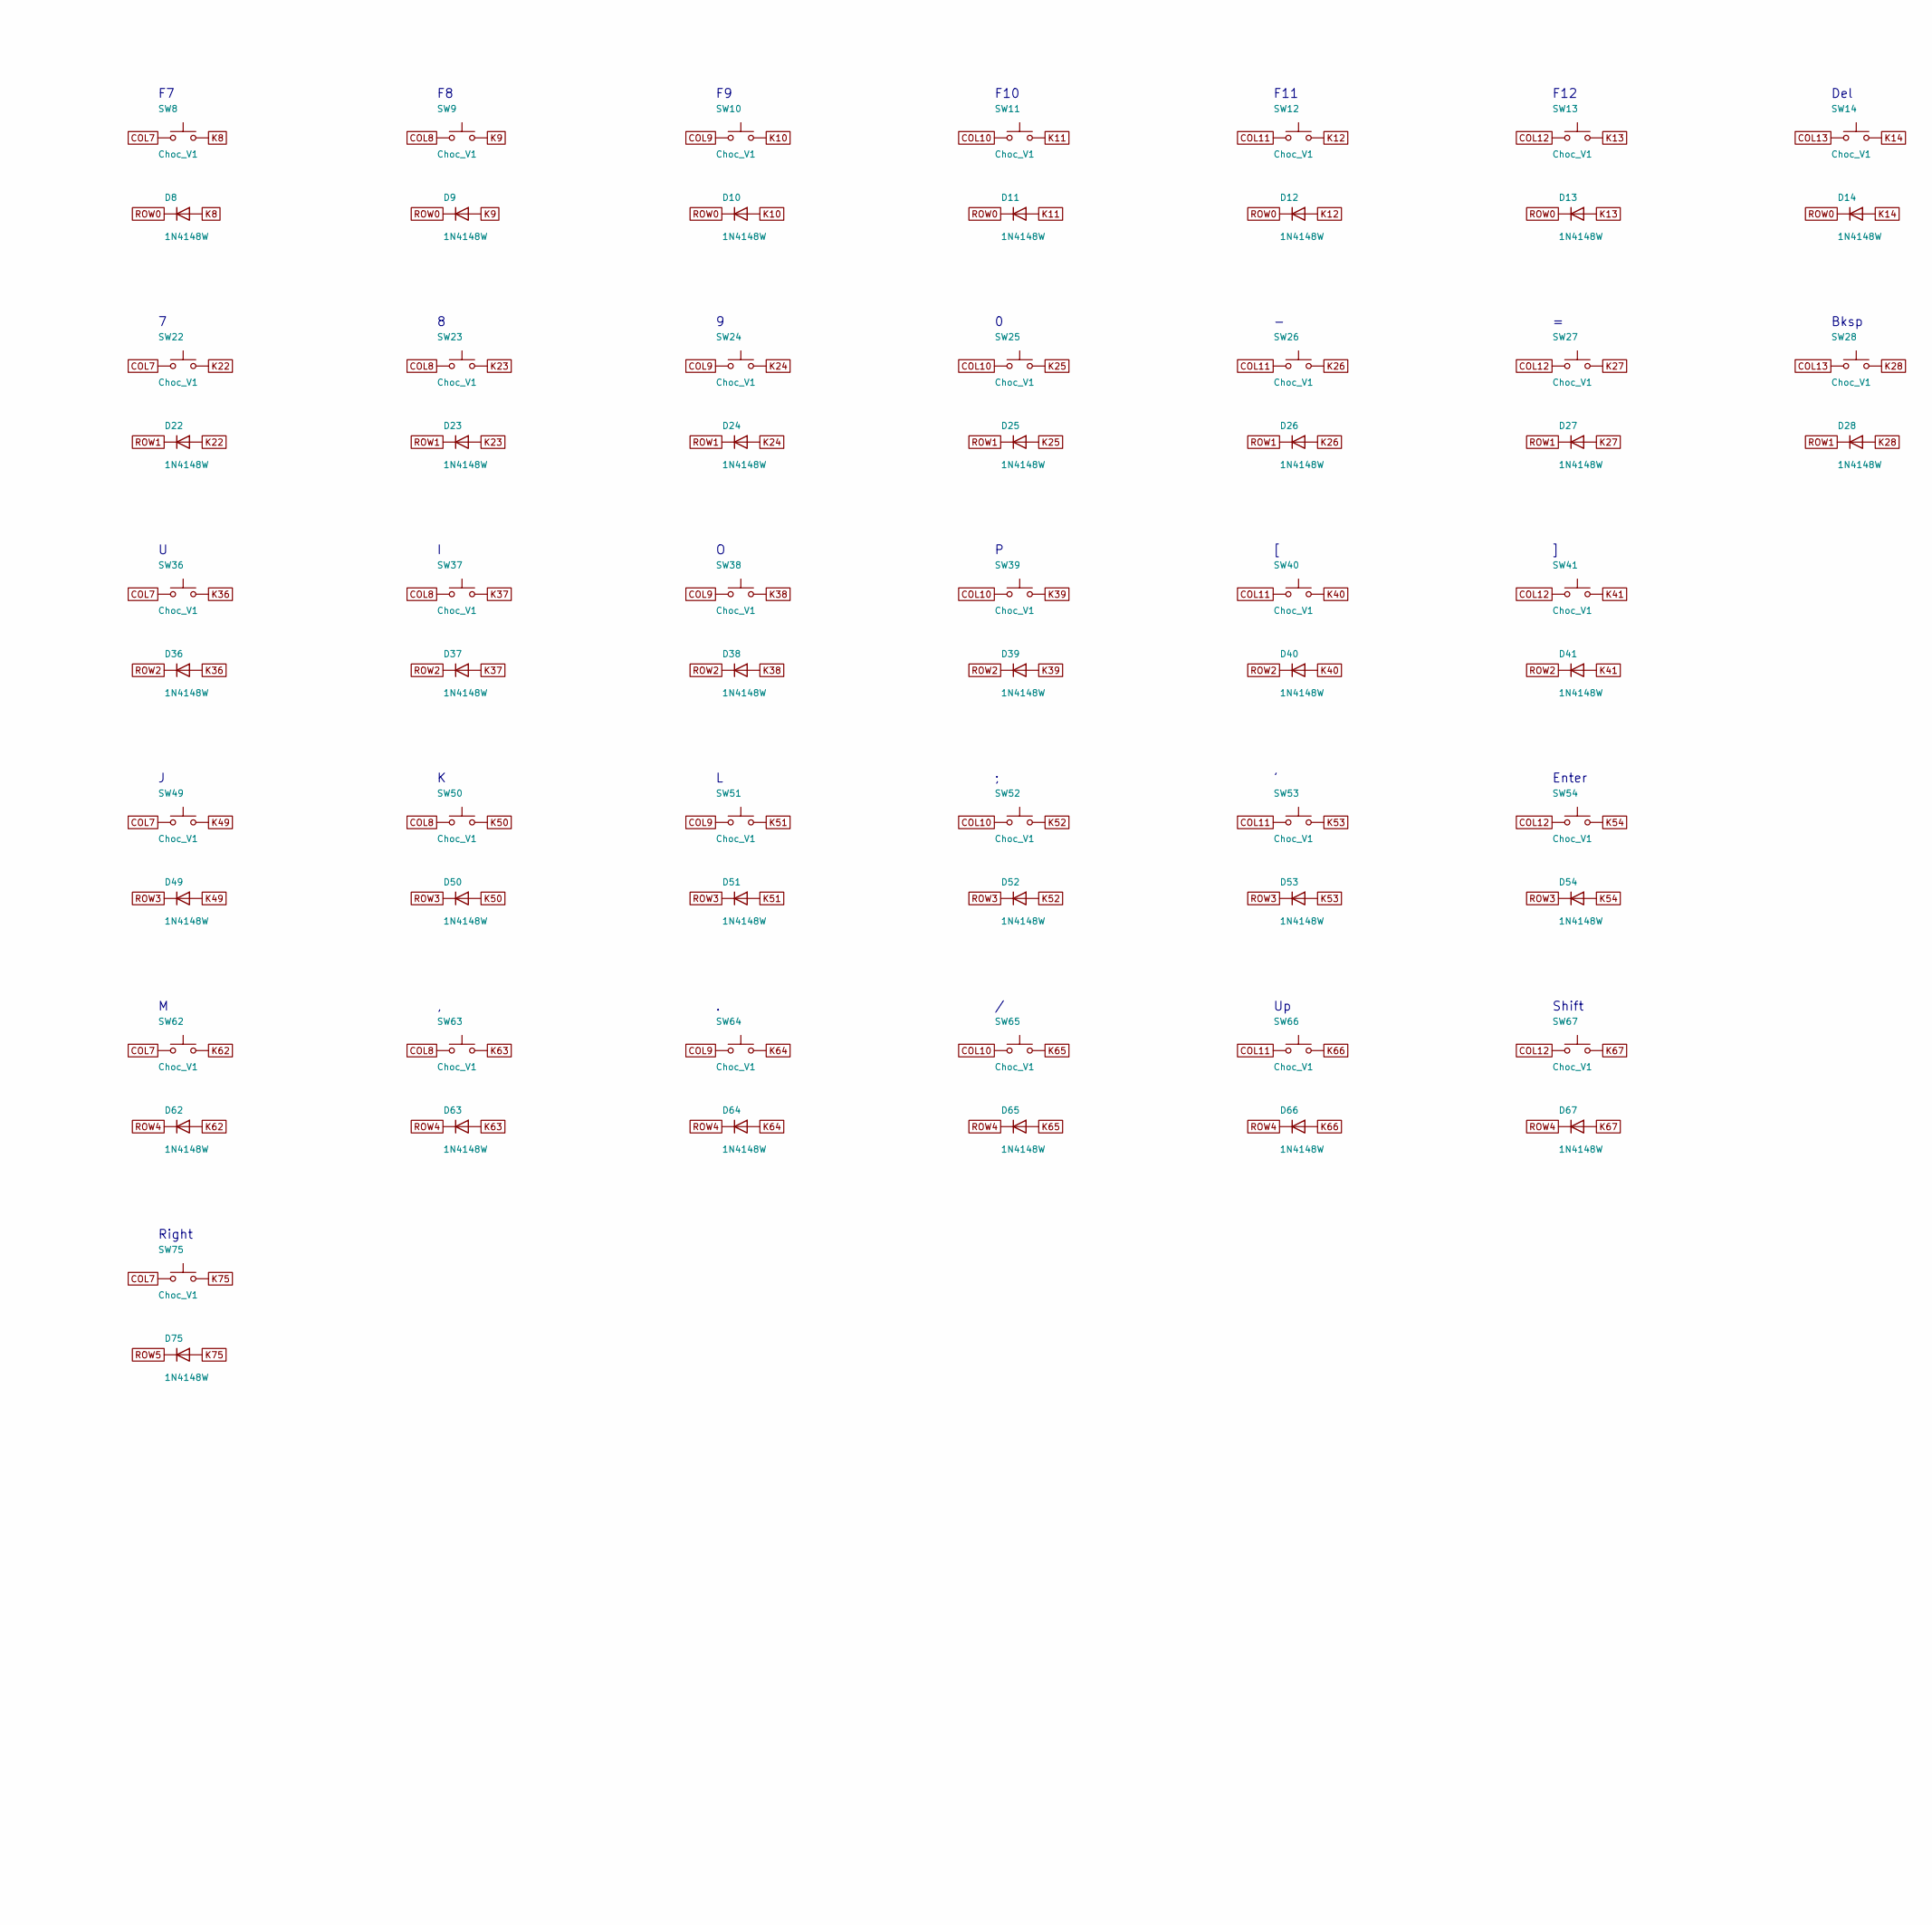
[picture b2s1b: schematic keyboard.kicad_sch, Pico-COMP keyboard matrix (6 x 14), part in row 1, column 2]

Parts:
D1, D2, D3, D4, D5, D6, D7, D8, D9, D10, D11, D12, D13, D14, D15, D16, D17, D18, D19, D20, D21, D22, D23, D24, D25, D26, D27, D28, D29, D30, D31, D32, D33, D34, D35, D36, D37, D38, D39, D40, D41, D42, D43, D44, D45, D46, D47, D48, D49, D50, D51, D52, D53, D54, D55, D56, D57, D58, D59, D60, D61, D62, D63, D64, D65, D66, D67, D68, D69, D70, D71, D72, D73, D74, D75: 1N4148W; D_SOD-123; MPN 1N4148W-7-F
FID1, FID2, FID3: Fiducial; Fiducial_1mm_Mask2mm
H1, H2, H3: M2.5; MountingHole_2.7mm_M2.5
J1: KB_MATRIX; PinHeader_1x20_P2.54mm_Horizontal
ST1: Stabilizer 2u; Kailh_Choc_Stabilizer_2u
ST2: Stabilizer 6u; Kailh_Choc_Stabilizer_6u
SW1, SW2, SW3, SW4, SW5, SW6, SW7, SW8, SW9, SW10, SW11, SW12, SW13, SW14, SW15, SW16, SW17, SW18, SW19, SW20, SW21, SW22, SW23, SW24, SW25, SW26, SW27, SW28, SW29, SW30, SW31, SW32, SW33, SW34, SW35, SW36, SW37, SW38, SW39, SW40, SW41, SW42, SW43, SW44, SW45, SW46, SW47, SW48, SW49, SW50, SW51, SW52, SW53, SW54, SW55, SW56, SW57, SW58, SW59, SW60, SW61, SW62, SW63, SW64, SW65, SW66, SW67, SW68, SW69, SW70, SW71, SW72, SW73, SW74, SW75: Choc_V1; Kailh_Choc_V1; MPN CPG135001D01

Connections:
COL0: J1.7, SW1.1, SW15.1, SW29.1, SW42.1, SW55.1, SW68.1
COL1: J1.8, SW2.1, SW16.1, SW30.1, SW43.1, SW56.1, SW69.1
COL2: J1.9, SW3.1, SW17.1, SW31.1, SW44.1, SW57.1, SW70.1
COL3: J1.10, SW4.1, SW18.1, SW32.1, SW45.1, SW58.1, SW71.1
COL4: J1.11, SW5.1, SW19.1, SW33.1, SW46.1, SW59.1, SW72.1
COL5: J1.12, SW6.1, SW20.1, SW34.1, SW47.1, SW60.1, SW73.1
COL6: J1.13, SW7.1, SW21.1, SW35.1, SW48.1, SW61.1, SW74.1
COL7: J1.14, SW8.1, SW22.1, SW36.1, SW49.1, SW62.1, SW75.1
COL8: J1.15, SW9.1, SW23.1, SW37.1, SW50.1, SW63.1
COL9: J1.16, SW10.1, SW24.1, SW38.1, SW51.1, SW64.1
COL10: J1.17, SW11.1, SW25.1, SW39.1, SW52.1, SW65.1
COL11: J1.18, SW12.1, SW26.1, SW40.1, SW53.1, SW66.1
COL12: J1.19, SW13.1, SW27.1, SW41.1, SW54.1, SW67.1
COL13: J1.20, SW14.1, SW28.1
K1: D1.2 (A), SW1.2
K2: D2.2 (A), SW2.2
K3: D3.2 (A), SW3.2
K4: D4.2 (A), SW4.2
K5: D5.2 (A), SW5.2
K6: D6.2 (A), SW6.2
K7: D7.2 (A), SW7.2
K8: D8.2 (A), SW8.2
K9: D9.2 (A), SW9.2
K10: D10.2 (A), SW10.2
K11: D11.2 (A), SW11.2
K12: D12.2 (A), SW12.2
K13: D13.2 (A), SW13.2
K14: D14.2 (A), SW14.2
K15: D15.2 (A), SW15.2
K16: D16.2 (A), SW16.2
K17: D17.2 (A), SW17.2
K18: D18.2 (A), SW18.2
K19: D19.2 (A), SW19.2
K20: D20.2 (A), SW20.2
K21: D21.2 (A), SW21.2
K22: D22.2 (A), SW22.2
K23: D23.2 (A), SW23.2
K24: D24.2 (A), SW24.2
K25: D25.2 (A), SW25.2
K26: D26.2 (A), SW26.2
K27: D27.2 (A), SW27.2
K28: D28.2 (A), SW28.2
K29: D29.2 (A), SW29.2
K30: D30.2 (A), SW30.2
K31: D31.2 (A), SW31.2
K32: D32.2 (A), SW32.2
K33: D33.2 (A), SW33.2
K34: D34.2 (A), SW34.2
K35: D35.2 (A), SW35.2
K36: D36.2 (A), SW36.2
K37: D37.2 (A), SW37.2
K38: D38.2 (A), SW38.2
K39: D39.2 (A), SW39.2
K40: D40.2 (A), SW40.2
K41: D41.2 (A), SW41.2
K42: D42.2 (A), SW42.2
K43: D43.2 (A), SW43.2
K44: D44.2 (A), SW44.2
K45: D45.2 (A), SW45.2
K46: D46.2 (A), SW46.2
K47: D47.2 (A), SW47.2
K48: D48.2 (A), SW48.2
K49: D49.2 (A), SW49.2
K50: D50.2 (A), SW50.2
K51: D51.2 (A), SW51.2
K52: D52.2 (A), SW52.2
K53: D53.2 (A), SW53.2
K54: D54.2 (A), SW54.2
K55: D55.2 (A), SW55.2
K56: D56.2 (A), SW56.2
K57: D57.2 (A), SW57.2
K58: D58.2 (A), SW58.2
K59: D59.2 (A), SW59.2
K60: D60.2 (A), SW60.2
K61: D61.2 (A), SW61.2
K62: D62.2 (A), SW62.2
K63: D63.2 (A), SW63.2
K64: D64.2 (A), SW64.2
K65: D65.2 (A), SW65.2
K66: D66.2 (A), SW66.2
K67: D67.2 (A), SW67.2
K68: D68.2 (A), SW68.2
K69: D69.2 (A), SW69.2
K70: D70.2 (A), SW70.2
K71: D71.2 (A), SW71.2
K72: D72.2 (A), SW72.2
K73: D73.2 (A), SW73.2
K74: D74.2 (A), SW74.2
K75: D75.2 (A), SW75.2
ROW0: D1.1 (K), D2.1 (K), D3.1 (K), D4.1 (K), D5.1 (K), D6.1 (K), D7.1 (K), D8.1 (K), D9.1 (K), D10.1 (K), D11.1 (K), D12.1 (K), D13.1 (K), D14.1 (K), J1.1
ROW1: D15.1 (K), D16.1 (K), D17.1 (K), D18.1 (K), D19.1 (K), D20.1 (K), D21.1 (K), D22.1 (K), D23.1 (K), D24.1 (K), D25.1 (K), D26.1 (K), D27.1 (K), D28.1 (K), J1.2
ROW2: D29.1 (K), D30.1 (K), D31.1 (K), D32.1 (K), D33.1 (K), D34.1 (K), D35.1 (K), D36.1 (K), D37.1 (K), D38.1 (K), D39.1 (K), D40.1 (K), D41.1 (K), J1.3
ROW3: D42.1 (K), D43.1 (K), D44.1 (K), D45.1 (K), D46.1 (K), D47.1 (K), D48.1 (K), D49.1 (K), D50.1 (K), D51.1 (K), D52.1 (K), D53.1 (K), D54.1 (K), J1.4
ROW4: D55.1 (K), D56.1 (K), D57.1 (K), D58.1 (K), D59.1 (K), D60.1 (K), D61.1 (K), D62.1 (K), D63.1 (K), D64.1 (K), D65.1 (K), D66.1 (K), D67.1 (K), J1.5
ROW5: D68.1 (K), D69.1 (K), D70.1 (K), D71.1 (K), D72.1 (K), D73.1 (K), D74.1 (K), D75.1 (K), J1.6

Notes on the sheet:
Key matrix: COL -> switch -> diode (anode) -> ROW. Scan: drive one ROW low, read COLs with pull-ups.
Esc
F10
F11
F12
Del
Bksp
Tab
Ctrl
Enter
Shift
Alt
Space
Left
Down
Right
Matrix connector (to mainboard J11) and mechanical

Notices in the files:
hardware/kicad/keyboard.kicad_pcb:
keyboard v1.0 © 2026 Aditya Kale
Pico COMP keyboard v1.0 © 2026 Aditya Kale
hardware/kicad/mainboard.kicad_pcb:
mainboard v1.0 © 2026 Aditya Kale
parts and their libraries:
MIT License, Copyright (c) 2026 Raspberry Pi Ltd.
